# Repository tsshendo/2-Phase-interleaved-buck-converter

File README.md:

# 2-Phase Interleaved Coupled-Inductor GaN Buck Converter — 72 V → 24 V, 1.1 kW

A two-phase interleaved synchronous buck converter using EPC2304 eGaN FETs and a TDK ERUC23
coupled inductor at 200 kHz. It started as the ECE 533 (Power Electronics Packaging, NC State,
Spring 2026) final project by Team MeGaNism and is being turned into a credit-card-size
(85.6 × 54 mm) PCB with an on-board analog controller and full protection, designed in KiCad 10.

| | |
|---|---|
| Input | 72 V nominal (64.8–79.2 V) |
| Output | 24 V, 46 A, 1.1 kW |
| Switching | 2 phases × 200 kHz, 180° interleaved |
| Target efficiency | ≥ 95 % |
| Board | 85.6 × 53.98 mm, 4-layer, 1.6 mm, JLCPCB |

## Status
See [`PROGRESS.md`](PROGRESS.md) for the current stage and decisions. The full design requirements are in
[`CLAUDE.md`](CLAUDE.md).

## Repository layout
```
kicad/ECE533_Guide/   KiCad 10 project (schematic, PCB, project-local footprints)
kicad/lib/vendor/     Vendor symbols/footprints: local only, see README inside
bom/                  Bill of materials
docs/                 Final report (PDF + DOCX), earlier report, design notes, datasheet links
sim/ltspice/          LTspice simulations (vendor models local only, see README inside)
fab/                  Fabrication outputs (added in Stage 5)
.github/workflows/    CI: KiCad ERC/DRC + schematic PDF on every push
```

## Getting started (local)
1. Clone the repo and install KiCad 10.0.
2. Download the vendor libraries into `kicad/lib/vendor/` (see its README). The project opens without them.
3. Open `kicad/ECE533_Guide/ECE533_Guide.kicad_pro`.

## Background
The original design, analysis (Q3D parasitics, ANSYS thermal/mechanical) and simulations are documented in
[`docs/ECE533_Final_Report.pdf`](docs/ECE533_Final_Report.pdf).

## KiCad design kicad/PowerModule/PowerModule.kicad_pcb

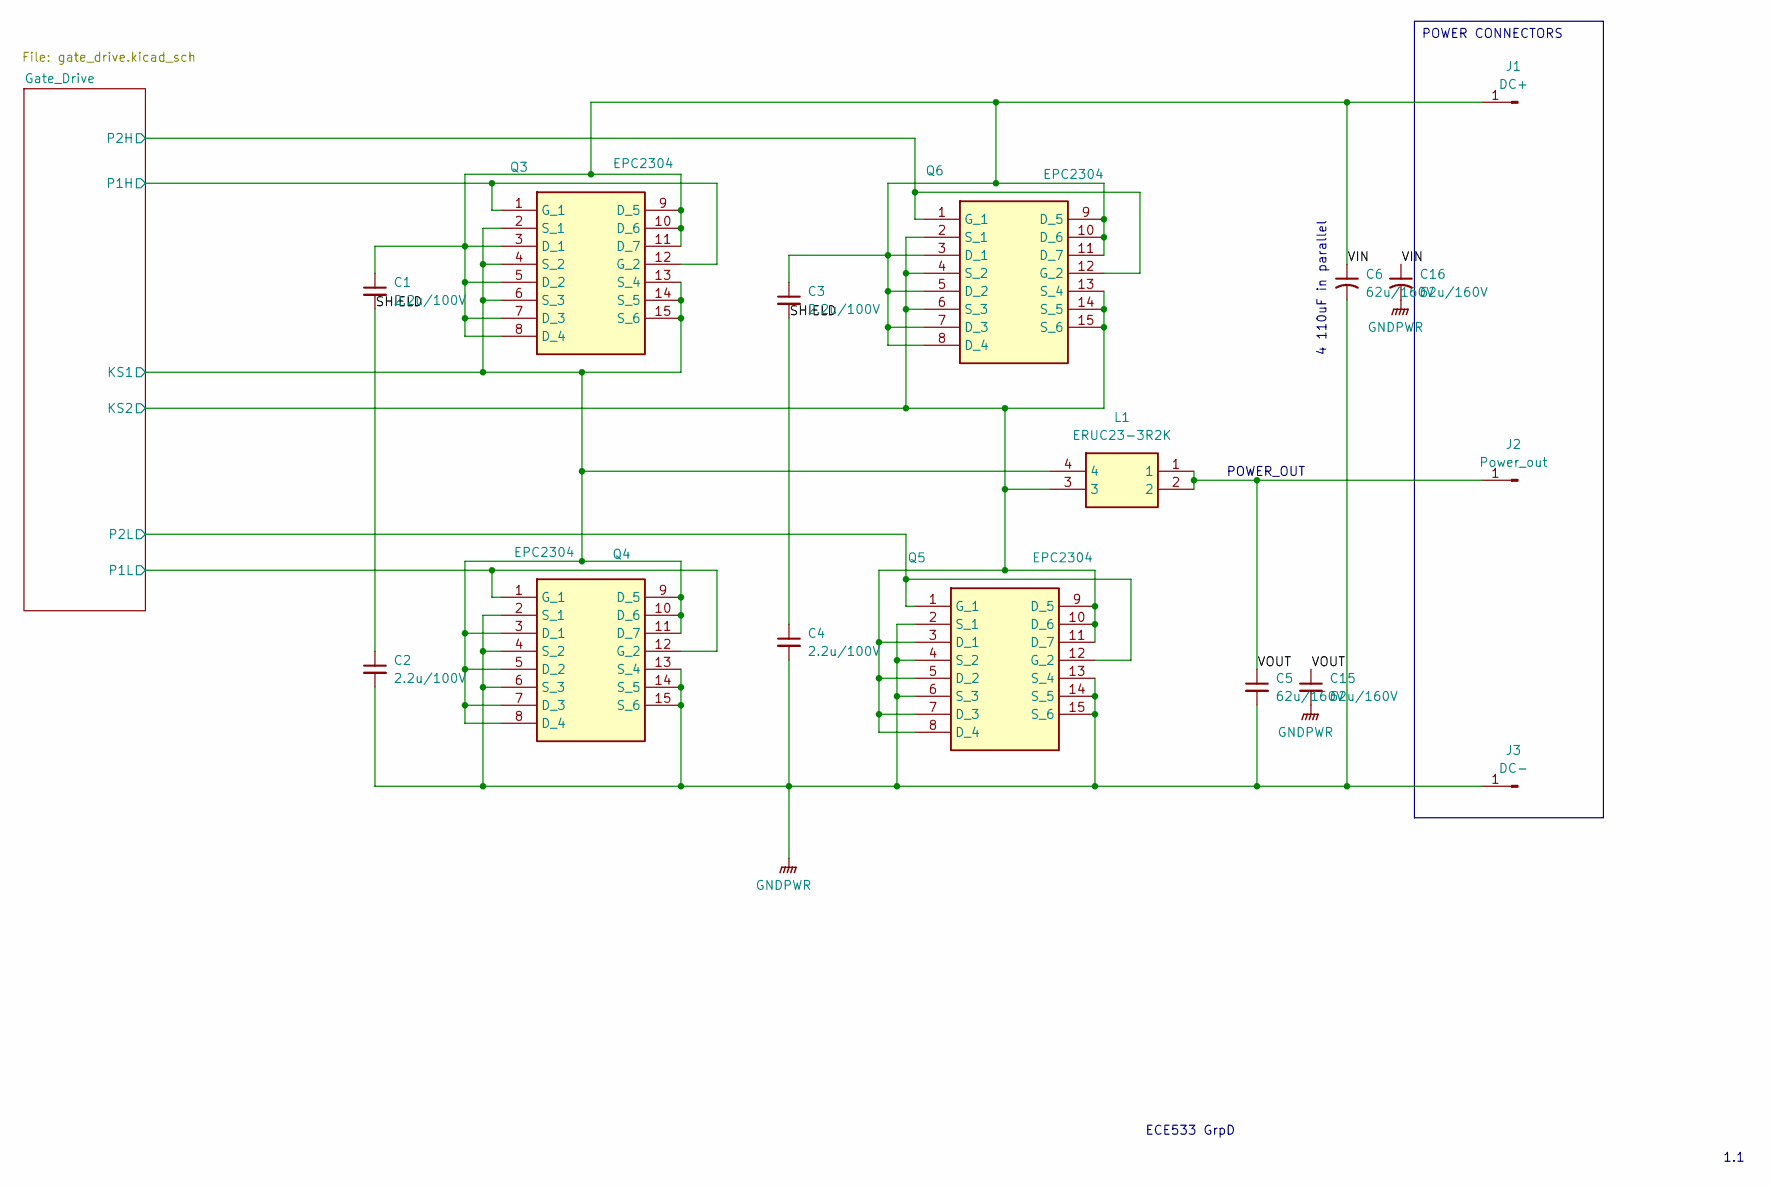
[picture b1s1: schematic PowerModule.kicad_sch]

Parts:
C1, C2, C3, C4: 2.2u/100V; C_0805_2012Metric; MPN GRM21BD72A225KE01L; LCSC C2981733
C5, C6, C15, C16: 62u/160V; CP_Radial_D10.0mm_P5.00mm; MPN EGXF161ELL620MJ25S
J1: DC+; Wurth_REDCUBE_74650194; MPN 74650194R
J2: Power_out; Wurth_REDCUBE_74650194; MPN 74650194R
J3: DC-; Wurth_REDCUBE_74650194; MPN 74650194R
L1: ERUC23-3R2K; TDK_ERUC23; Manufacturer_Part_Number ERUC23-3R2K; Mouser Part Number 871-ERUC23-3R2K
Q3, Q4, Q5, Q6: EPC2304; EPC2304_QFN-7_3x5mm_15pin; Manufacturer_Part_Number EPC2304; LCSC C6549215

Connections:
/Gate_Drive/KS1: L1.4, Q3.2 (S_1), Q3.4 (S_2), Q3.6 (S_3), Q3.13 (S_4), Q3.14 (S_5), Q3.15 (S_6), Q4.3 (D_1), Q4.5 (D_2), Q4.7 (D_3), Q4.8 (D_4), Q4.9 (D_5), Q4.10 (D_6), Q4.11 (D_7); also elsewhere on the board
/Gate_Drive/KS2: L1.3, Q5.3 (D_1), Q5.5 (D_2), Q5.7 (D_3), Q5.8 (D_4), Q5.9 (D_5), Q5.10 (D_6), Q5.11 (D_7), Q6.2 (S_1), Q6.4 (S_2), Q6.6 (S_3), Q6.13 (S_4), Q6.14 (S_5), Q6.15 (S_6); also elsewhere on the board
/Gate_Drive/P1H: Q3.1 (G_1), Q3.12 (G_2); also elsewhere on the board
/Gate_Drive/P1L: Q4.1 (G_1), Q4.12 (G_2); also elsewhere on the board
/Gate_Drive/P2H: Q6.1 (G_1), Q6.12 (G_2); also elsewhere on the board
/Gate_Drive/P2L: Q5.1 (G_1), Q5.12 (G_2); also elsewhere on the board
/SHIELD: C1.2, C2.1, C3.2, C4.1
/VIN: C1.1, C3.1, C6.1, C16.1, J1.1, Q3.3 (D_1), Q3.5 (D_2), Q3.7 (D_3), Q3.8 (D_4), Q3.9 (D_5), Q3.10 (D_6), Q3.11 (D_7), Q6.3 (D_1), Q6.5 (D_2), Q6.7 (D_3), Q6.8 (D_4), Q6.9 (D_5), Q6.10 (D_6), Q6.11 (D_7)
/VOUT: C5.1, C15.1, J2.1, L1.1, L1.2
GNDPWR: C2.2, C4.2, C5.2, C6.2, C15.2, C16.2, J3.1, Q4.2 (S_1), Q4.4 (S_2), Q4.6 (S_3), Q4.13 (S_4), Q4.14 (S_5), Q4.15 (S_6), Q5.2 (S_1), Q5.4 (S_2), Q5.6 (S_3), Q5.13 (S_4), Q5.14 (S_5), Q5.15 (S_6); also elsewhere on the board

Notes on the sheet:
POWER_OUT
ECE533 GrpD
1.1
4 110uF in parallel
POWER CONNECTORS

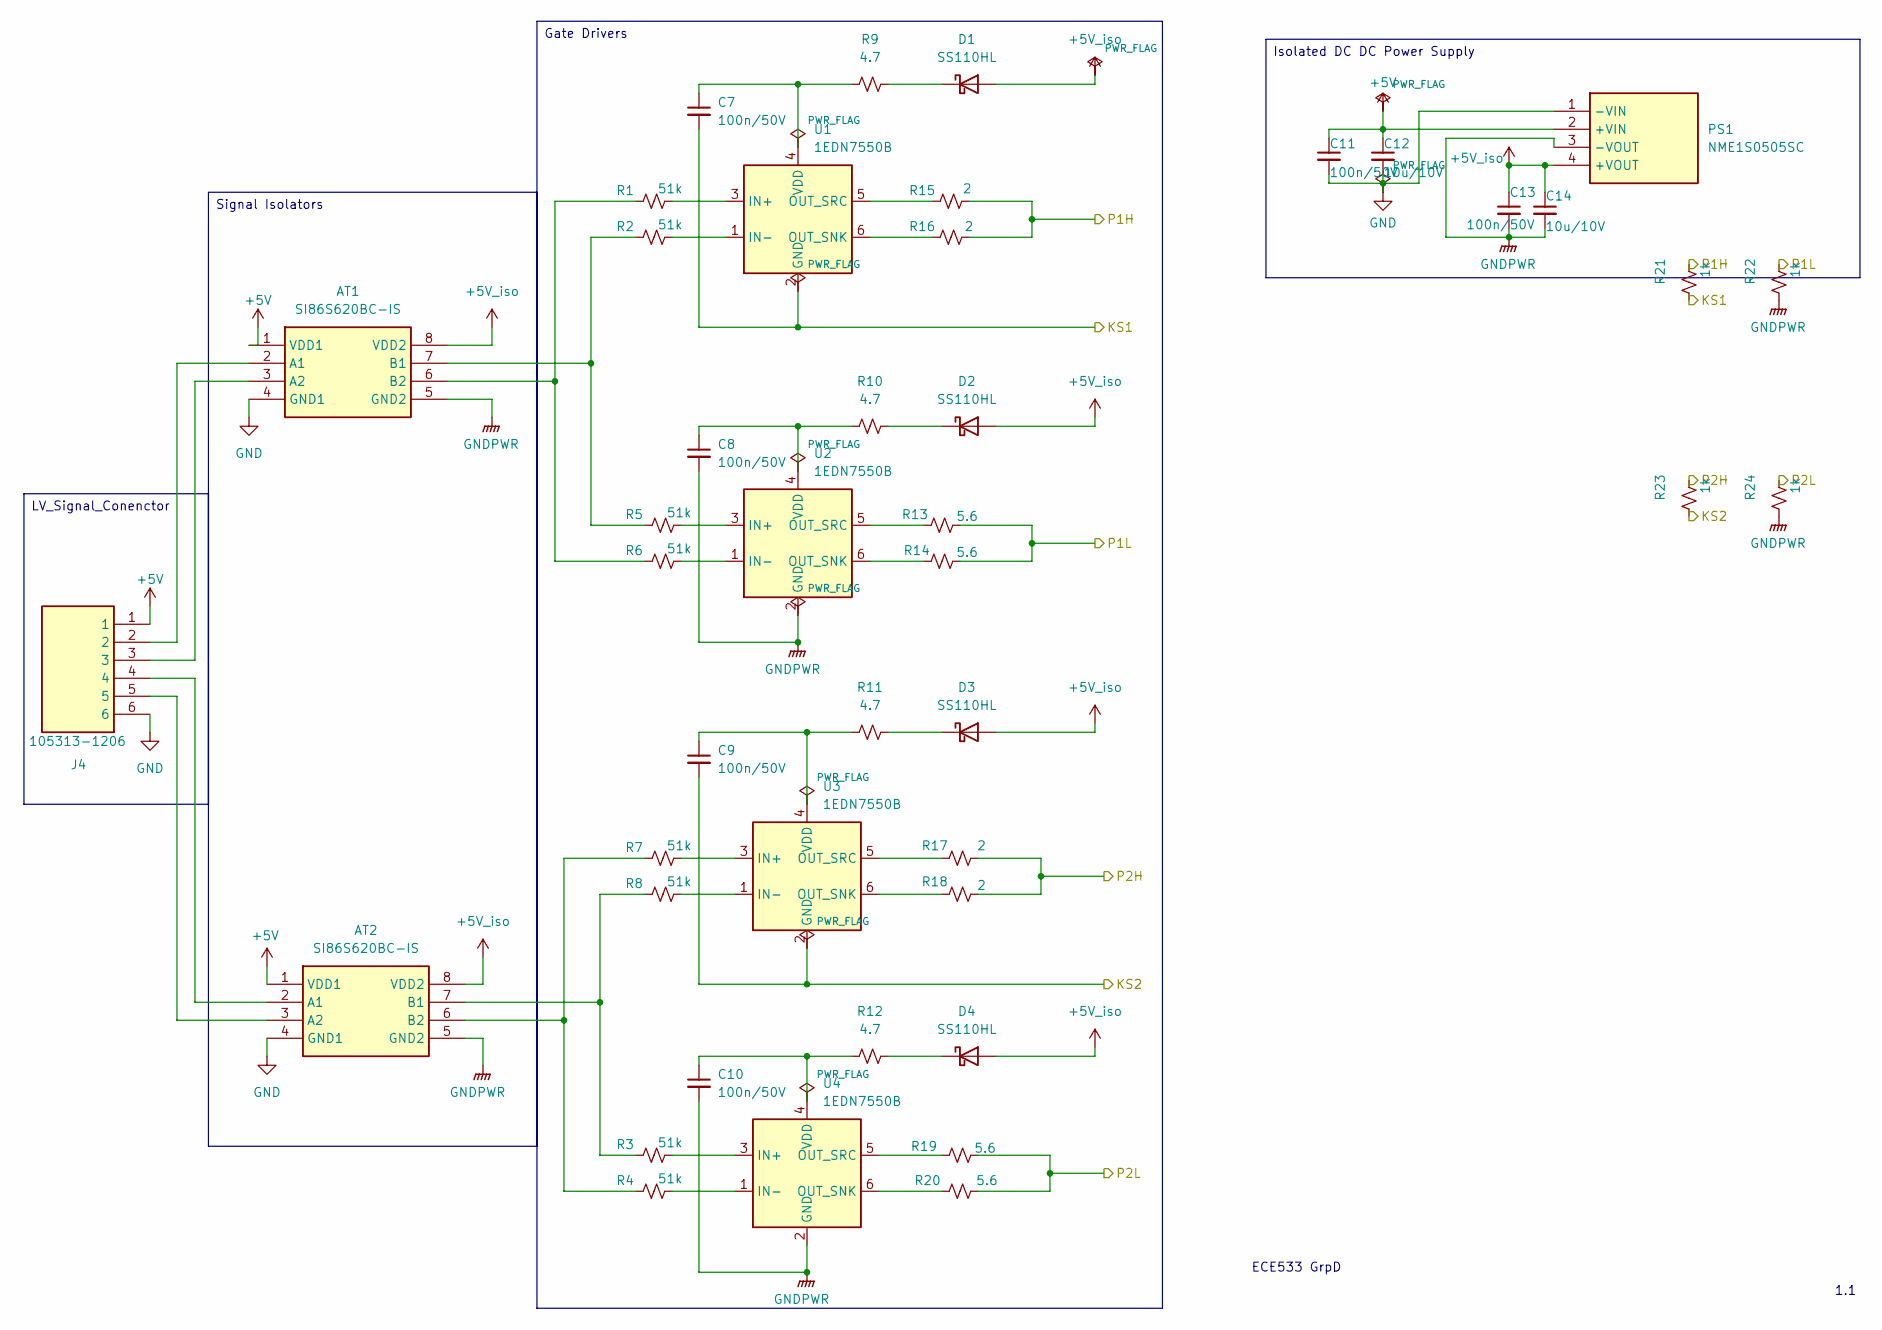
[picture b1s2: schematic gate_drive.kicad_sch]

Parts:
AT1, AT2: SI86S620BC-IS; SOIC-8_3.9x4.9mm_P1.27mm; Manufacturer_Part_Number SI86S620BC-IS; Mouser Part Number 873-SI86S620BC-IS
C7, C8, C9, C10, C11, C13: 100n/50V; C_0603_1608Metric; MPN GRM188R71H104KA93D; LCSC C77055
C12, C14: 10u/10V; C_0805_2012Metric; MPN GRM21BR71A106KE51L; LCSC C86038
D1, D2, D3, D4: SS110HL; D_SOD-123F; MPN SS110HL-TP; LCSC C19996385
J4: 105313-1206; Molex_Nano-Fit_105313-1206_RA; Manufacturer_Part_Number 105313-1206; Mouser Part Number 538-105313-1206
PS1: NME1S0505SC; Murata_NME1S_SIP-4; Manufacturer_Part_Number NME1S0505SC; Mouser Part Number 580-NME1S0505SC
R1, R2, R3, R4, R5, R6, R7, R8: 51k; R_0603_1608Metric; MPN RC0603FR-0751KL
R9, R10, R11, R12: 4.7; R_0603_1608Metric; MPN RC0603FR-074R7L
R13, R14, R19, R20: 5.6; R_0603_1608Metric; MPN RC0603FR-075R6L
R15, R16, R17, R18: 2; R_0603_1608Metric; MPN RC0603FR-072RL
R21, R22, R23, R24: 1k; R_0603_1608Metric; MPN RC0603FR-071KL
U1, U2, U3, U4: 1EDN7550B; SOT-23-6; MPN 1EDN7550BXTSA1

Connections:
+5V: AT1.1 (VDD1), AT2.1 (VDD1), C11.1, C12.1, J4.1, PS1.2 (+VIN)
+5V_iso: AT1.8 (VDD2), AT2.8 (VDD2), C13.1, C14.1, D1.2 (A), D2.2 (A), D3.2 (A), D4.2 (A), PS1.4 (+VOUT)
/Gate_Drive/KS1: C7.2, R21.2, U1.2 (GND); also elsewhere on the board
/Gate_Drive/KS2: C9.2, R23.2, U3.2 (GND); also elsewhere on the board
/Gate_Drive/P1H: R15.1, R16.1, R21.1; also elsewhere on the board
/Gate_Drive/P1L: R13.1, R14.1, R22.1; also elsewhere on the board
/Gate_Drive/P2H: R17.1, R18.1, R23.1; also elsewhere on the board
/Gate_Drive/P2L: R19.1, R20.1, R24.1; also elsewhere on the board
GND: AT1.4 (GND1), AT2.4 (GND1), C11.2, C12.2, J4.6, PS1.1 (-VIN)
GNDPWR: AT1.5 (GND2), AT2.5 (GND2), C8.2, C10.2, C13.2, C14.2, PS1.3 (-VOUT), R22.2, R24.2, U2.2 (GND), U4.2 (GND); also elsewhere on the board
unnamed: AT1.2 (A1), J4.2
unnamed: AT1.3 (A2), J4.3
unnamed: AT1.7 (B1), R2.2, R5.2
unnamed: AT1.6 (B2), R1.2, R6.2
unnamed: AT2.2 (A1), J4.4
unnamed: AT2.3 (A2), J4.5
unnamed: AT2.7 (B1), R3.2, R8.2
unnamed: AT2.6 (B2), R4.2, R7.2
unnamed: D1.1 (K), R9.1
unnamed: D2.1 (K), R10.1
unnamed: D3.1 (K), R11.1
unnamed: D4.1 (K), R12.1
unnamed: R1.1, U1.3 (IN+)
unnamed: R2.1, U1.1 (IN-)
unnamed: R16.2, U1.6 (OUT_SNK)
unnamed: R15.2, U1.5 (OUT_SRC)
unnamed: C7.1, R9.2, U1.4 (VDD)
unnamed: R5.1, U2.3 (IN+)
unnamed: R6.1, U2.1 (IN-)
unnamed: R14.2, U2.6 (OUT_SNK)
unnamed: R13.2, U2.5 (OUT_SRC)
unnamed: C8.1, R10.2, U2.4 (VDD)
unnamed: R7.1, U3.3 (IN+)
unnamed: R8.1, U3.1 (IN-)
unnamed: R18.2, U3.6 (OUT_SNK)
unnamed: R17.2, U3.5 (OUT_SRC)
unnamed: C9.1, R11.2, U3.4 (VDD)
unnamed: R3.1, U4.3 (IN+)
unnamed: R4.1, U4.1 (IN-)
unnamed: R20.2, U4.6 (OUT_SNK)
unnamed: R19.2, U4.5 (OUT_SRC)
unnamed: C10.1, R12.2, U4.4 (VDD)

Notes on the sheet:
ECE533 GrpD
1.1
LV_Signal_Conenctor
Isolated DC DC Power Supply
Gate Drivers
Signal Isolators

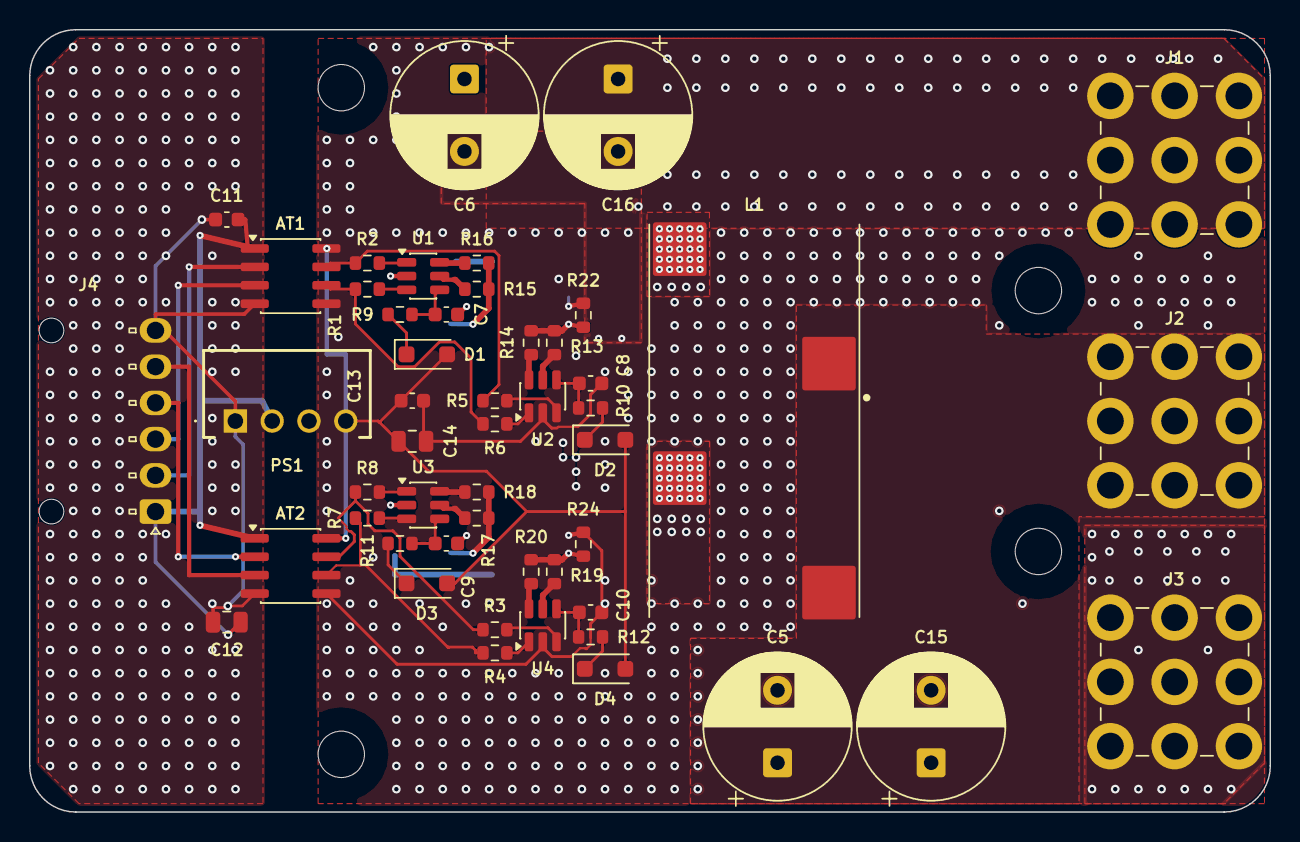
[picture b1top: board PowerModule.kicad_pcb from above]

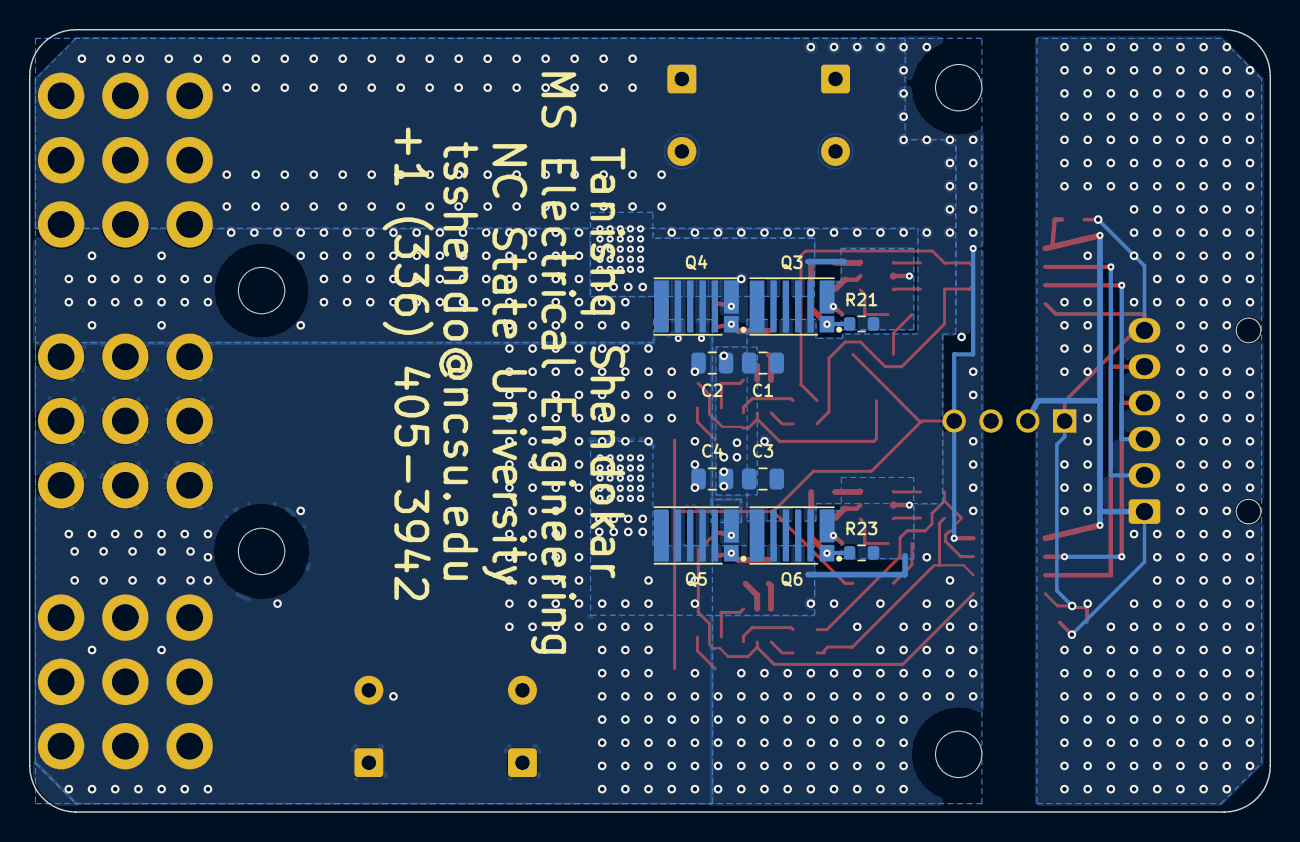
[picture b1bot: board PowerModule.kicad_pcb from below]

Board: 4 copper layers, 85.6 x 54.0 mm, 64 parts (10 on the bottom side), 45 nets.

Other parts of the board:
H1, H2, H3, H4: M3 heatsink; MountingHole_3.2mm_M3

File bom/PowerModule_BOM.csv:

Item,Qty,Reference designators,Value,Manufacturer part number,Manufacturer,Digi-Key PN,LCSC PN,Footprint,Side,Notes
1,2,"AT1,AT2",SI86S620BC-IS,SI86S620BC-IS,Skyworks,863-SI86S620BC-IS-ND,C7363570,SOIC-8_3.9x4.9mm_P1.27mm,Top,Report part (base schematic)
2,4,"C1,C2,C3,C4",2.2u/100V,GRM21BD72A225KE01L,Murata,490-GRM21BD72A225KE01LCT-ND,C2981733,C_0805_2012Metric,Bottom,Report part (base schematic)
3,4,"C5,C6,C15,C16",62u/160V,EGXF161ELL620MJ25S,Chemi-Con,,,CP_Radial_D10.0mm_P5.00mm,Top,"Bulk split into 2 x half value per position (GXF 160 V, 10 x 25 mm); Digi-Key PN and stock to confirm"
4,6,"C7,C8,C9,C10,C11,C13",100n/50V,GRM188R71H104KA93D,Murata,,C77055,C_0603_1608Metric,Top,Same part as the main board BOM
5,2,"C12,C14",10u/10V,GRM21BR71A106KE51L,Murata,,C86038,C_0805_2012Metric,Top,Same part as the main board BOM
6,4,"D1,D2,D3,D4",SS110HL,SS110HL-TP,MCC,353-SS110HL-TPCT-ND,C19996385,D_SOD-123F,Top,Report part (base schematic)
7,1,J1,DC+,74650194R,Wurth Elektronik,,,Wurth_REDCUBE_74650194,Top,Same part as the main board BOM
8,1,J2,Power_out,74650194R,Wurth Elektronik,,,Wurth_REDCUBE_74650194,Top,Same part as the main board BOM
9,1,J3,DC-,74650194R,Wurth Elektronik,,,Wurth_REDCUBE_74650194,Top,Same part as the main board BOM
10,1,J4,105313-1206,105313-1206,Molex,WM14975-ND,C17656275,Molex_Nano-Fit_105313-1206_RA,Top,Report part (base schematic)
11,1,L1,ERUC23-3R2K,ERUC23-3R2K,TDK,495-ERUC23-3R2KCT-ND,,TDK_ERUC23,Top,Report part (base schematic)
12,1,PS1,NME1S0505SC,NME1S0505SC,Murata,811-NME1S0505SC-ND,C39128444,Murata_NME1S_SIP-4,Top,Report part (base schematic)
13,4,"Q3,Q4,Q5,Q6",EPC2304,EPC2304,EPC,917-EPC2304CT-ND,C6549215,EPC2304_QFN-7_3x5mm_15pin,Bottom,Report part (base schematic)
14,8,"R1,R2,R3,R4,R5,R6,R7,R8",51k,RC0603FR-0751KL,YAGEO,,,R_0603_1608Metric,Top,Same part as the main board BOM
15,4,"R9,R10,R11,R12",4.7,RC0603FR-074R7L,YAGEO,,,R_0603_1608Metric,Top,Same part as the main board BOM
16,4,"R13,R14,R19,R20",5.6,RC0603FR-075R6L,YAGEO,,,R_0603_1608Metric,Top,Same part as the main board BOM
17,4,"R15,R16,R17,R18",2,RC0603FR-072RL,YAGEO,,,R_0603_1608Metric,Top,Same part as the main board BOM
18,4,"R21,R22,R23,R24",1k,RC0603FR-071KL,YAGEO,,,R_0603_1608Metric,Top + Bottom,"Gate pull-downs (report LTspice model): R21/R23 bottom, R22/R24 top"
19,4,"U1,U2,U3,U4",1EDN7550B,1EDN7550BXTSA1,Infineon,,,SOT-23-6,Top,Report driver (base schematic); Digi-Key PN and stock to confirm
20,1,(mechanical),Z60-12.7B heatsink,Z60-12.7B,Alpha Novatech,,,4 x M3 holes H1-H4,Bottom,"Pedestal 3.0 mm over the FET block, insulating TIM"

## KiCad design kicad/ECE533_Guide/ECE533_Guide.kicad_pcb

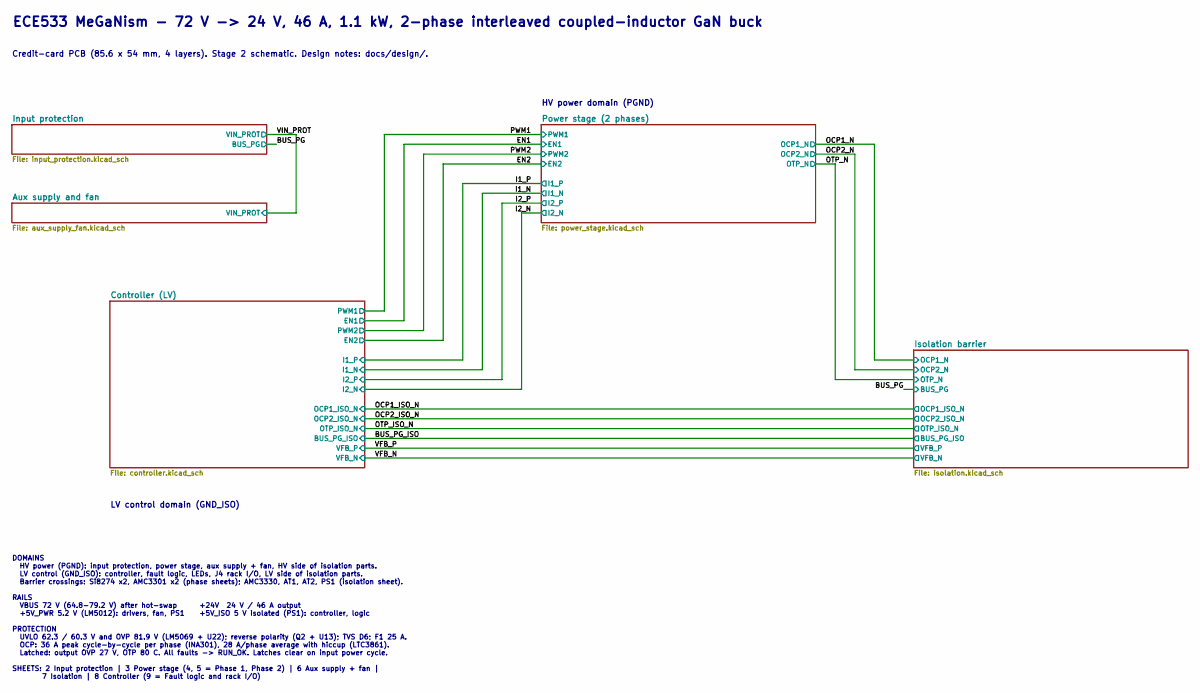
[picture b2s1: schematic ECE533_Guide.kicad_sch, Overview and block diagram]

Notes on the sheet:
ECE533 MeGaNism - 72 V -> 24 V, 46 A, 1.1 kW, 2-phase interleaved coupled-inductor GaN buck
Credit-card PCB (85.6 x 54 mm, 4 layers). Stage 2 schematic. Design notes: docs/design/.
HV power domain (PGND)
LV control domain (GND_ISO)
DOMAINS HV power (PGND): input protection, power stage, aux supply + fan, HV side of isolation parts. LV control (GND_ISO): controller, fault logic, LEDs, J4 rack I/O, LV side of isolation parts. Barrier crossings: Si8274 x2, AMC3301 x2 (phase sheets); AMC3330, AT1, AT2, PS1 (isolation sheet). RAIL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

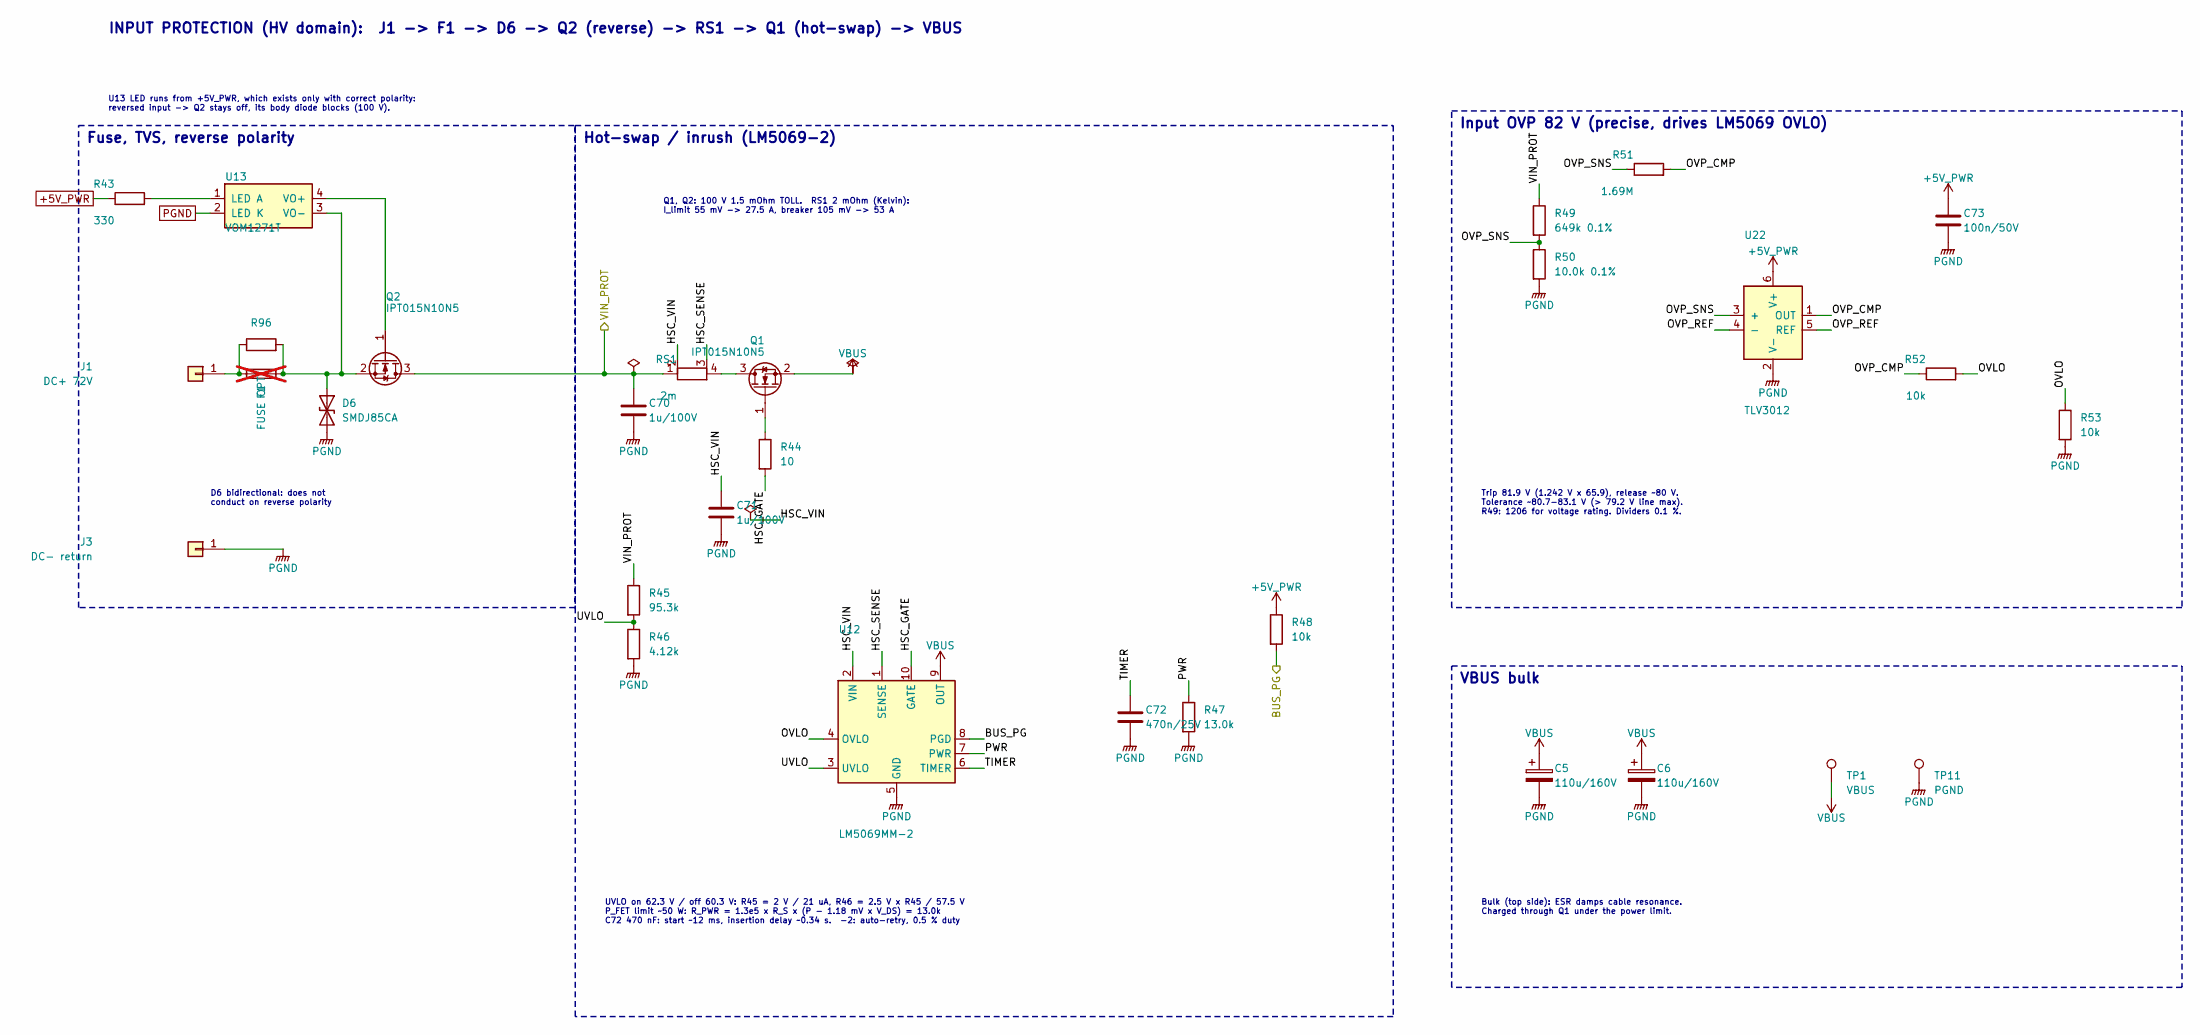
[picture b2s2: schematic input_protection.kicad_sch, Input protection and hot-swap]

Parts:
C5, C6: 110u/160V; CP_Radial_D12.5mm_P5.00mm; MPN EGXF161ELL111MK25S; LCSC C1598290
C70, C71: 1u/100V; C_0805_2012Metric; MPN CC0805KKX7R0BB105; LCSC C5370002
C72: 470n/25V; C_0603_1608Metric; MPN GRM188R71E474KA12D; LCSC C77052
C73: 100n/50V; C_0603_1608Metric; MPN GRM188R71H104KA93D; LCSC C77055
D6: SMDJ85CA; D_SMC; MPN SMDJ85CA; LCSC C1978008
F1: FUSE OPT; Fuse_Littelfuse_NANO2_456; MPN not fitted; not fitted
J1: DC+ 72V; Wurth_REDCUBE_74650194; MPN 74650194R
J3: DC- return; Wurth_REDCUBE_74650194; MPN 74650194R
Q1, Q2: IPT015N10N5; Infineon_PG-HSOF-8-1; MPN IPT015N10N5; LCSC C108964
R43: 330; R_0603_1608Metric; MPN RC0603FR-07330RL
R44: 10; R_0603_1608Metric; MPN RC0603FR-0710RL
R45: 95.3k; R_1206_3216Metric; MPN RC1206FR-0795K3L
R46: 4.12k; R_0603_1608Metric; MPN RC0603FR-074K12L
R47: 13.0k; R_0603_1608Metric; MPN RC0603FR-0713KL
R48, R52, R53: 10k; R_0603_1608Metric; MPN RC0603FR-0710KL
R49: 649k 0.1%; R_1206_3216Metric; MPN ERA-8AEB6493V
R50: 10.0k 0.1%; R_0603_1608Metric; MPN ERA-3AEB1002V
R51: 1.69M; R_0603_1608Metric; MPN RC0603FR-071M69L
R96: 0R 100A; R_2512_CSS2H; MPN CSS2H-2512C-000
RS1: 2m; R_2512_Kelvin; MPN CSS2H-2512R-2L00F
TP1: VBUS; TestPoint_Pad_D1.5mm; MPN Test pad (bare copper)
TP11: PGND; TestPoint_Pad_D1.5mm; MPN Test pad (bare copper)
U12: LM5069MM-2; MSOP-10_3x3mm_P0.5mm; MPN LM5069MM-2/NOPB
U13: VOM1271T; SOP-4_3.8x4.1mm_P2.54mm; MPN VOM1271T; LCSC C146286
U22: TLV3012; SOT-23-6; MPN TLV3012AIDBVR; LCSC C62505

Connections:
+5V_PWR: C73.1, R43.1, R48.1, U22.6 (V+); also elsewhere on the board
/BUS_PG: R48.2, U12.8 (PGD); also elsewhere on the board
/Input protection/HSC_GATE: R44.2, U12.10 (GATE)
/Input protection/HSC_SENSE: RS1.3, U12.1 (SENSE)
/Input protection/HSC_VIN: C71.1, RS1.2, U12.2 (VIN)
/Input protection/OVLO: R52.2, R53.1, U12.4 (OVLO)
/Input protection/OVP_CMP: R51.2, R52.1, U22.1 (OUT)
/Input protection/OVP_REF: U22.4 (-), U22.5 (REF)
/Input protection/OVP_SNS: R49.2, R50.1, R51.1, U22.3 (+)
/Input protection/PWR: R47.1, U12.7 (PWR)
/Input protection/TIMER: C72.1, U12.6 (TIMER)
/Input protection/UVLO: R45.2, R46.1, U12.3 (UVLO)
/VIN_PROT: C70.1, Q2.3 (D), R45.1, R49.1, RS1.1; also elsewhere on the board
unnamed: D6.1 (A1), F1.2, Q2.2 (S), R96.2, U13.3 (VO-)
unnamed: F1.1, J1.1, R96.1
unnamed: Q1.3 (D), RS1.4
unnamed: Q1.1 (G), R44.1
unnamed: Q2.1 (G), U13.4 (VO+)
unnamed: R43.2, U13.1 (LED A)
PGND: C5.2, C6.2, C70.2, C71.2, C72.2, C73.2, D6.2 (A2), J3.1, R46.2, R47.2, R50.2, R53.2, TP11.1, U12.5 (GND), U13.2 (LED K), U22.2 (V-); also elsewhere on the board
VBUS: C5.1, C6.1, Q1.2 (S), TP1.1, U12.9 (OUT); also elsewhere on the board

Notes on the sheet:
INPUT PROTECTION (HV domain): J1 -> F1 -> D6 -> Q2 (reverse) -> RS1 -> Q1 (hot-swap) -> VBUS
D6 bidirectional: does not conduct on reverse polarity
U13 LED runs from +5V_PWR, which exists only with correct polarity: reversed input -> Q2 stays off, its body diode blocks (100 V).
Fuse, TVS, reverse polarity
Q1, Q2: 100 V 1.5 mOhm TOLL. RS1 2 mOhm (Kelvin): I_limit 55 mV -> 27.5 A, breaker 105 mV -> 53 A
UVLO on 62.3 V / off 60.3 V: R45 = 2 V / 21 uA, R46 = 2.5 V x R45 / 57.5 V P_FET limit ~50 W: R_PWR = 1.3e5 x R_S x (P - 1.18 mV x V_DS) = 13.0k C72 470 nF: start ~12 ms, insertion delay ~0.34 s. -2: auto-retry, 0.5 % duty
Hot-swap / inrush (LM5069-2)
Trip 81.9 V (1.242 V x 65.9), release ~80 V. Tolerance ~80.7-83.1 V (> 79.2 V line max). R49: 1206 for voltage rating. Dividers 0.1 %.
Input OVP 82 V (precise, drives LM5069 OVLO)
Bulk (top side): ESR damps cable resonance. Charged through Q1 under the power limit.
VBUS bulk

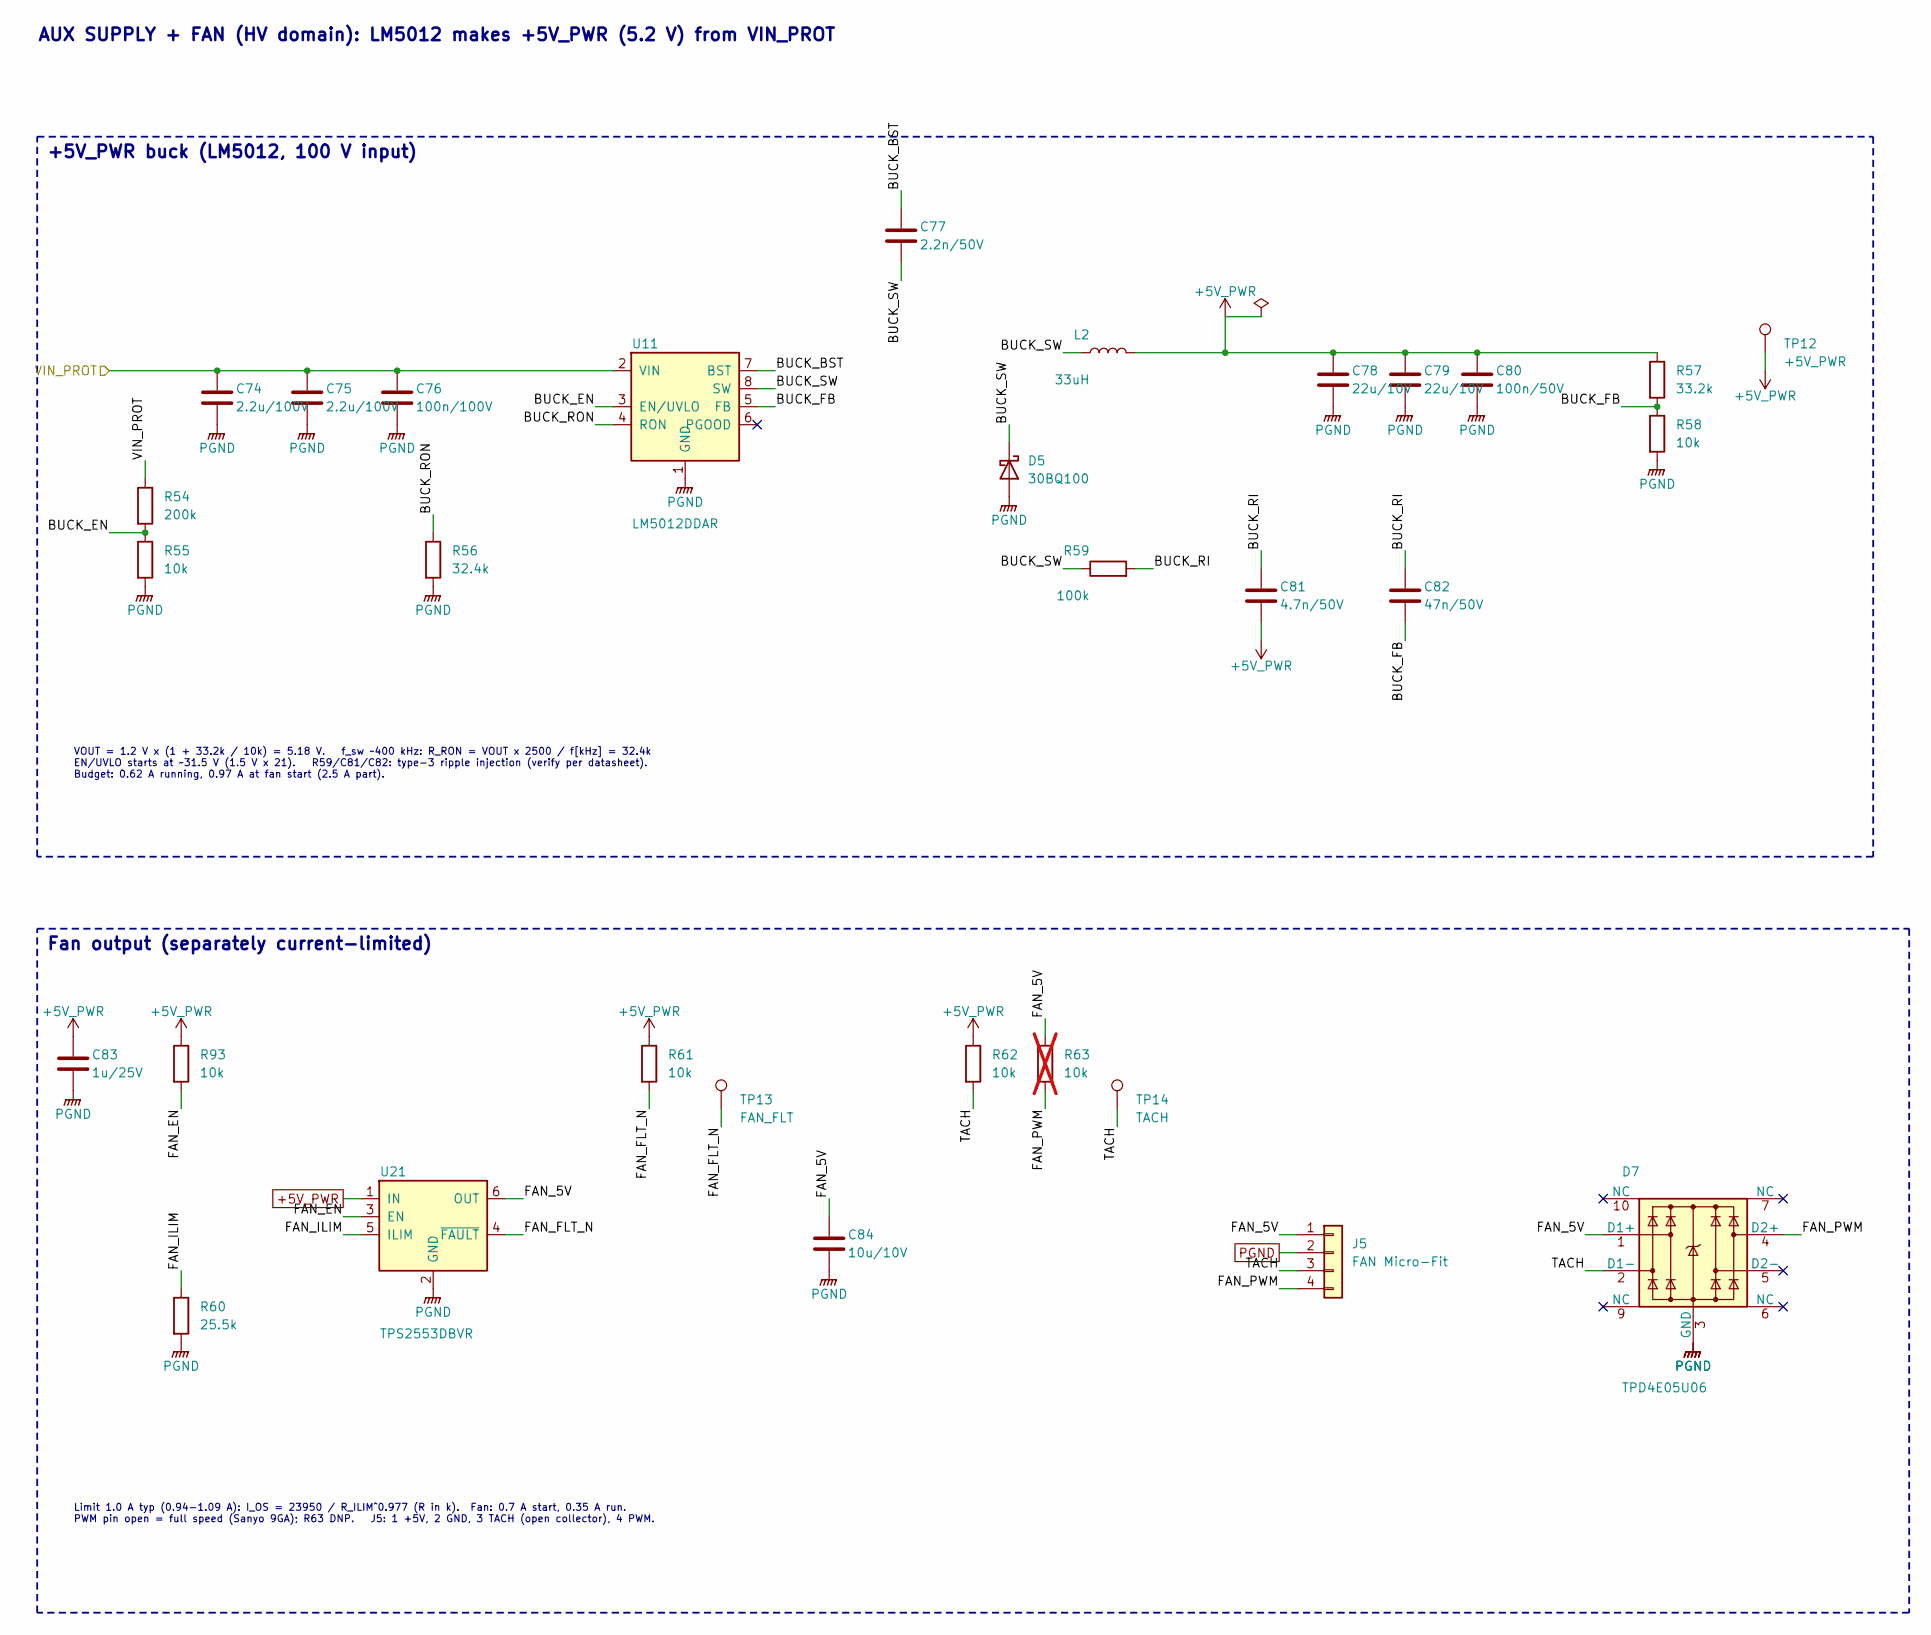
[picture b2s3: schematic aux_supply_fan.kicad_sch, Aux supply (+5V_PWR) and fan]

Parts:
C74, C75: 2.2u/100V; C_0805_2012Metric; MPN GRM21BD72A225KE01L; LCSC C2981733
C76: 100n/100V; C_0603_1608Metric; MPN GRM188R72A104KA35D; LCSC C77058
C77: 2.2n/50V; C_0603_1608Metric; MPN GRM188R71H222KA01D; LCSC C86023
C78, C79: 22u/10V; C_1206_3216Metric; MPN GRM31CR71A226KE15L; LCSC C91604
C80: 100n/50V; C_0603_1608Metric; MPN GRM188R71H104KA93D; LCSC C77055
C81: 4.7n/50V; C_0603_1608Metric; MPN GRM188R71H472KA01D; LCSC C77057
C82: 47n/50V; C_0603_1608Metric; MPN GRM188R71H473KA61D; LCSC C86027
C83: 1u/25V; C_0603_1608Metric; MPN GRM188R71E105KA12D; LCSC C86020
C84: 10u/10V; C_0805_2012Metric; MPN GRM21BR71A106KE51L; LCSC C86038
D5: 30BQ100; D_SMC; MPN VS-30BQ100TRPBF
D7: TPD4E05U06; USON-10_2.5x1.0mm_P0.5mm; MPN TPD4E05U06DQAR; LCSC C138714
J5: FAN Micro-Fit; Molex_Micro-Fit_3.0_43650-0400_1x04_P3.00mm_Horizontal; MPN 43650-0400; LCSC C277684
L2: 33uH; L_Coilcraft_XAL7070-XXX; MPN XAL7070-333MEB
R54: 200k; R_1206_3216Metric; MPN RC1206FR-07200KL
R55, R58, R61, R62, R93: 10k; R_0603_1608Metric; MPN RC0603FR-0710KL
R56: 32.4k; R_0603_1608Metric; MPN RC0603FR-0732K4L
R57: 33.2k; R_0603_1608Metric; MPN RC0603FR-0733K2L
R59: 100k; R_0603_1608Metric; MPN RC0603FR-07100KL
R60: 25.5k; R_0603_1608Metric; MPN RC0603FR-0725K5L
R63: 10k; R_0603_1608Metric; MPN RC0603FR-0710KL; not fitted
TP12: +5V_PWR; TestPoint_Pad_D1.5mm; MPN Test pad (bare copper)
TP13: FAN_FLT; TestPoint_Pad_D1.5mm; MPN Test pad (bare copper)
TP14: TACH; TestPoint_Pad_D1.5mm; MPN Test pad (bare copper)
U11: LM5012DDAR; HSOP-8-1EP_3.9x4.9mm_P1.27mm_EP2.41x3.1mm; MPN LM5012DDAR; LCSC C6079494
U21: TPS2553DBVR; SOT-23-6; MPN TPS2553DBVR; LCSC C55266

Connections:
+5V_PWR: C78.1, C79.1, C80.1, C81.2, C83.1, L2.2, R57.1, R61.1, R62.1, R93.1, TP12.1, U21.1 (IN); also elsewhere on the board
/Aux supply and fan/BUCK_BST: C77.1, U11.7 (BST)
/Aux supply and fan/BUCK_EN: R54.2, R55.1, U11.3 (EN/UVLO)
/Aux supply and fan/BUCK_FB: C82.2, R57.2, R58.1, U11.5 (FB)
/Aux supply and fan/BUCK_RI: C81.1, C82.1, R59.2
/Aux supply and fan/BUCK_RON: R56.1, U11.4 (RON)
/Aux supply and fan/BUCK_SW: C77.2, D5.1 (K), L2.1, R59.1, U11.8 (SW)
/Aux supply and fan/FAN_5V: C84.1, D7.1 (D1+), J5.1, R63.1, U21.6 (OUT)
/Aux supply and fan/FAN_EN: R93.2, U21.3 (EN)
/Aux supply and fan/FAN_FLT_N: R61.2, TP13.1, U21.4 (~FAULT)
/Aux supply and fan/FAN_ILIM: R60.1, U21.5 (ILIM)
/Aux supply and fan/FAN_PWM: D7.4 (D2+), J5.4, R63.2
/Aux supply and fan/TACH: D7.2 (D1-), J5.3, R62.2, TP14.1
/VIN_PROT: C74.1, C75.1, C76.1, R54.1, U11.2 (VIN); also elsewhere on the board
PGND: C74.2, C75.2, C76.2, C78.2, C79.2, C80.2, C83.2, C84.2, D5.2 (A), D7.3 (GND), D7.8 (GND), J5.2, R55.2, R56.2, R58.2, R60.2, U11.1 (GND), U11.9 (GND), U21.2 (GND); also elsewhere on the board

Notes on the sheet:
AUX SUPPLY + FAN (HV domain): LM5012 makes +5V_PWR (5.2 V) from VIN_PROT
VOUT = 1.2 V x (1 + 33.2k / 10k) = 5.18 V. f_sw ~400 kHz: R_RON = VOUT x 2500 / f[kHz] = 32.4k EN/UVLO starts at ~31.5 V (1.5 V x 21). R59/C81/C82: type-3 ripple injection (verify per datasheet). Budget: 0.62 A running, 0.97 A at fan start (2.5 A part).
+5V_PWR buck (LM5012, 100 V input)
Limit 1.0 A typ (0.94-1.09 A): I_OS = 23950 / R_ILIM^0.977 (R in k). Fan: 0.7 A start, 0.35 A run. PWM pin open = full speed (Sanyo 9GA); R63 DNP. J5: 1 +5V, 2 GND, 3 TACH (open collector), 4 PWM.
Fan output (separately current-limited)
